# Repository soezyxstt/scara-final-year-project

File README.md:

# 2-DOF SCARA Robot | Final Year Project

Embedded control and web software for a planar 2-DOF SCARA robot used as an educational control-system demonstrator.

The repository includes ESP32 firmware, a browser HMI, shared telemetry definitions, experiment tools, documentation, and selected datasets.

## System

- Joint 1: DC motor with closed-loop control
- Joint 2: stepper motor
- Controller: ESP32 DevKit V1
- HMI: Next.js in the browser
- Communication: Web Serial at 921600 baud

The firmware implements PID control, a tracking differentiator, trapezoidal trajectories, and switchable inertia, Coriolis, and gravity compensation.

## Highlights

- Closed-loop embedded control
- Cartesian trajectory generation and inverse kinematics
- Shared telemetry contract between firmware and HMI
- Browser-based tuning, monitoring, and experiment analysis
- Reproducible experiment export pipeline

## Architecture

```text
SCARA hardware
      │
      ▼
    ESP32
  control + trajectory
      │
   Web Serial
      │
      ▼
 Browser HMI
 operation + telemetry + analysis
```

## Structure

```text
analysis/          experiment export tools
data/experiments/  selected datasets
firmware/          PlatformIO firmware
hmi/               Next.js HMI
shared/telemetry/  shared packet schema
docs/              technical documentation
```

## Run the HMI

```bash
npm install
npm run gen
npm run dev
```

Use Chrome or Edge for Web Serial.

## Firmware

```powershell
scara.bat compile
scara.bat upload
scara.bat all
```

## Experiments

| Experiment | Comparison |
|---|---|
| EXP-1 | tracking differentiator off vs on |
| EXP-2 | dynamic compensation off vs inertia on |
| EXP-3 | inertia only vs inertia + Coriolis |
| EXP-4 | gravity compensation off vs on |
| EXP-5 | trapezoidal profile off vs on |

Recreate selected exports with:

```powershell
python analysis/export_experiment_csv.py ..\results\tugasakhir.db
```

See `data/README.md` and `docs/` for technical details.

Never commit credentials, environment files, or raw application databases. Verify workspace limits and engage the emergency stop before working on the mechanism.

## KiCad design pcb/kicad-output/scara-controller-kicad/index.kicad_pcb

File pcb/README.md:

# SCARA Controller PCB (tscircuit)

ESP32 DevKitC "motherboard" that sockets an A4988 stepper driver carrier and
an LM2596 buck module (no-LED variant), regulates power, and breaks out the
potentiometer, quadrature-encoder, and off-board L298N control signals.

This board does **not** require you to solder the MCU or the driver chip by
hand — you buy the ESP32 DevKitC, the A4988 carrier, and the LM2596 module
separately, and they plug into headers/sockets on this PCB (same idea as a
RAMPS/CNC-shield board).

**Pin assignments match `firmware/include/config.h` 1:1.** The Joint 1 DC
motor is driven by an **off-board L298N H-bridge** — this PCB does not carry
the H-bridge itself, it breaks out 12V/5V/GND plus the three control signals
(IN3=IO16, IN4=IO17, EN=IO18) to the `J_DC` header. A new 4-pin `J_ENC`
header adds a quadrature encoder (A=IO25, B=IO26) for closed-loop Joint 1
feedback.

**Grounding:** a solid bottom-layer copper pour tied to `net.GND` acts as the
ground plane; every GND pad ties to it. Rails are named nets (`V12`, `V5`,
`V3V3`, `GND`) so the schematic renders clean power/ground flags.

> **On bottom-layer "slots":** the bottom layer looks busy, but most of those
> traces are the **GND membership tree** — they carry `net.GND` and merge into
> the pour (same net), so they do **not** cut the plane. The only true plane
> slots are a handful of non-GND escapes routed on the bottom to clear the dense
> through-hole pad fields (notably `STEP` and the `5V` dip). They are deliberate
> and load-bearing (moving them to the top layer would re-introduce pad-field
> DRC violations), and at this board's signal speeds (`STEP`/PWM ≤ tens of kHz)
> the return-path impact of these short slots is negligible. `DIR` and `V12`
> were routed along the board margin **outside** the pour boundary, so they
> don't slot it at all.

## What's been verified

This design has been built and checked with tscircuit's own DRC/connectivity
checker (`@tscircuit/core`) — **0 errors**: no shorts, no missing nets, no
pad-clearance violations, no footprint overlaps. What has **not** been
verified: exact manufacturable footprints for the ESP32 DevKitC header pitch
and the A4988 socket pitch — those use best-known nominal dimensions, but you
should confirm them against your actual boards before ordering copper (see
"Before you fab" below).

## Setup (on your own machine — this needs internet access)

```bash
# 1. Install bun (tscircuit's CLI requires it)
curl -fsSL https://bun.sh/install | bash

# 2. Install dependencies
cd .temp
bun install --ignore-scripts   # --ignore-scripts works around a sharp/Windows install crash

# 3. Live preview (schematic + PCB + 3D, hot reload like Next.js)
npx tscircuit dev
# open http://localhost:3020
```

## Files

- `index.tsx` — the board. Default export, this is what `tsci dev` renders.
- `validate.tsx` — headless DRC/connectivity check script. Run with
  `bun run validate.tsx`.
- `package.json`, `tsconfig.json` — minimal config to run both of the above.

## Bill of materials (besides the PCB itself)

| Ref | Part | Notes |
|---|---|---|
| U1 | ESP32 DevKitC (38-pin) | Socketed via 2× 1×19, 2.54mm female headers, 25.4mm row spacing. Onboard USB-UART, 3.3V LDO, EN/BOOT buttons — none of that is duplicated on this PCB. |
| A4988 | A4988 stepper driver carrier (Pololu or clone) | Joint 2. Plugs into the A4988 socket. MS1/MS2/MS3 are tied to 3V3 on the board (fixed 1/16 step); EN tied to GND (always enabled); RESET+SLEEP tied together to 3V3. |
| U2 | LM2596 adjustable buck module — no-LED version | 12V→5V. Modeled on the real full-size "LM2596S ADJ" module (~43×21mm): IN+/IN- on the left edge, OUT+/OUT- on the right edge, current flows left-to-right. |
| PWR_IN | 3-pin terminal (stand-in for a 5.5×2.1mm female DC barrel jack) | 12V supply in. VCC (center pin), GND (sleeve), and the normally-closed switch/detect leg (tied to GND). |
| STEPPER | 4-pin terminal | Joint 2 stepper motor coils (1A/1B/2A/2B). |
| J_DC | 6-pin header | Off-board **L298N** breakout for the Joint 1 DC motor: V12, GND, IN3=IO16, IN4=IO17, ENA=IO18, V5. |
| POT1 | 3-pin header | Joint 1 (DC) position pot → IO39. Brush-EMI filtering is done off-board (external LPF); no on-board bypass cap on this revision. |
| POT2 | 3-pin header | Joint 2 (stepper) position pot → IO36. No on-board bypass cap on this revision. |
| ENC | 4-pin header | Joint 1 quadrature encoder: 3V3, GND, ENC_A=IO25, ENC_B=IO26. |
| J_EXP | 8-pos 3.5mm screw terminal | Spare-GPIO expansion for future sensors: 3V3, GND, IO21 (I2C SDA), IO22 (I2C SCL), IO19, IO23, IO5, IO4 (ADC2). All firmware-untouched. IO5 is boot-strapping (idles HIGH) — don't pull LOW at power-on. (IO27/IO34 were remapped here onto the ESP32 right column so expansion nets don't cross the DIP.) |

## ESP32 GPIO map (matches `firmware/include/config.h`)

| Signal | GPIO | Why |
|---|---|---|
| Stepper STEP | IO14 | A4988 step pulse (J2) |
| Stepper DIR | IO12 | A4988 direction (J2) |
| Stepper MS1/MS2/MS3 | tied to 3V3 | fixed 1/16 microstep — firmware never toggles them, so they are hardwired (frees IO33/32/35 and removes the IO35 input-only bug) |
| DC motor IN3 | IO16 | L298N direction A (J1, via J_DC) |
| DC motor IN4 | IO17 | L298N direction B (J1, via J_DC) |
| DC motor EN | IO18 | L298N PWM speed, LEDC (J1, via J_DC) |
| Joint 2 pot wiper | IO36 | ADC1_CH0 — readable while WiFi is on |
| Joint 1 pot wiper | IO39 | ADC1_CH3 — RC-filtered (brush EMI) |
| Encoder A | IO25 | Joint 1 quadrature encoder (new) |
| Encoder B | IO26 | Joint 1 quadrature encoder (new) |

Four rails exist on this board: `V12`, `V5`, `V3V3`, and `GND`. The DevKitC's
own onboard regulator produces 3.3V, which is pulled back out of its `3V3` pin
(the `V3V3` net) to power the A4988 logic (`VDD`), the hardwired MS pins, the
pots, and the encoder header. `GND` is a solid bottom-layer copper pour.

## What changed in the manufacturing revision

This revision realigns the board to the **actual firmware** (`config.h`),
which drives a Joint 1 DC motor and reads two pots — earlier drafts had the
pins and the DC-motor handling wrong.

- **Pins now match `config.h` 1:1**: STEP=IO14, DIR=IO12, J2 pot=IO36, J1
  pot=IO39, and DC-motor control IN3/IN4/EN=IO16/IO17/IO18. (Previous draft
  had STEP=IO25, pots on IO34/35, encoder on IO16/17 — none of which the
  firmware uses.)
- **DC motor restored as an off-board L298N**: added the `J_DC` 6-pin header
  (V12/GND/IN3/IN4/ENA/V5). The firmware actively PWMs an L298N for Joint 1,
  so the previous "this board does not drive a DC motor" stance was wrong.
  The H-bridge stays off-board; only power + the three control signals are
  broken out.
- **Encoder kept, moved off the conflict**: `ENC` (A/B) now uses IO25/IO26
  because IO16/IO17 are taken by the L298N. This adds the closed-loop Joint 1
  feedback the new board was built for.
- **Microstep pins hardwired**: MS1/MS2/MS3 tie to 3V3 on the PCB (fixed 1/16
  step). This frees IO33/IO32/IO35 and removes the latent bug where MS3 sat on
  input-only IO35 and could not be driven.
- **Ground plane**: added a solid bottom-layer `copperpour` on `net.GND` and
  replaced the fragile hand-routed star-ground chain with per-pad ties to the
  net. Rails are named nets so the schematic gets proper power/ground flags.
- **J1 analog filtering is off-board**: the main brush-EMI low-pass is handled
  by an off-board LPF, so neither an on-board series resistor nor a local bypass
  cap is fitted at IO39 — this avoids double-filtering and excess ADC source
  impedance. (Earlier drafts listed `C_POT1`/`C_POT2` bypass caps; they were
  never placed in the layout and have been dropped from the docs to match.)
- **Spacing & size**: the `PWR_IN` silkscreen no longer overhangs the board
  edge, and the LM2596↔ESP32 gap was opened up. The board is tightly packed
  at **96×66mm** — width is set by the 43mm LM2596 + ESP32 + right-edge
  terminals; the rest of the empty space was trimmed out.
- **Expansion terminal**: added `J_EXP`, an 8-position 3.5mm screw terminal
  breaking out spare GPIO (I2C + digital + an ADC1 analog-in) plus 3V3/GND for
  future sensors, with per-pin silkscreen labels.

## Before you fab (i.e. before you actually order copper)

1. **Swap in real footprints.** The DevKitC header pitch/spacing and the
   A4988 socket pitch were built from best-known nominal dimensions. Once
   you're in `tsci dev` with real internet, use the part-import dialog to
   confirm:
   - your specific ESP32 DevKitC variant's row spacing (commonly 25.4mm, but
     some narrower clones use ~22.86mm)
   - your A4988/Pololu module's exact pin spacing
   - a real female DC barrel jack footprint in place of the `PWR_IN`
     3-pin terminal placeholder
2. **Trace widths.** Per-trace width is set with the **`thickness`** prop on
   `<trace>` (the `pcbRouteWidth` prop is silently ignored by this autorouter —
   don't use it). The board `minTraceWidth` floor is **0.5mm**; power/coil nets
   are explicitly fatter: `V12` 0.8mm, stepper coils 0.8mm, `5V` 0.6mm, `V3V3`
   0.5mm. `GND`'s real return current rides the bottom pour.
3. **Pour review.** Review the GND pour stitching (the vias tying top traces to
   the bottom plane — the small dots you see in the layout view) before fab.
4. **Thermal reliefs (hand-soldering DFM).** tscircuit's `<copperpour>` ties
   through-hole GND pads to the bottom plane with a **solid** connection — it
   does **not** emit thermal-relief spokes (the prop set is `connectsTo` only;
   no thermal option exists). Almost every part here is a hand-soldered THT
   module, so a solid plane connection makes GND pins act as a heatsink and
   risks cold joints. Before fab, either (a) enable thermal reliefs on the GND
   plane in your CAM/Gerber tool (target: 0.254mm spoke width, 0.254mm air gap,
   0.508mm expansion), or (b) use a temperature-controlled iron with extra dwell
   on GND pins. This is a known tscircuit limitation, not a layout error.
5. **Firmware cleanup (optional).** Since MS1/2/3 are hardwired, you can drop
   the `MS1/MS2/MS3` defines and their `pinMode`/`digitalWrite` calls from the
   firmware — they now drive nothing. Harmless to leave, but tidier to remove.

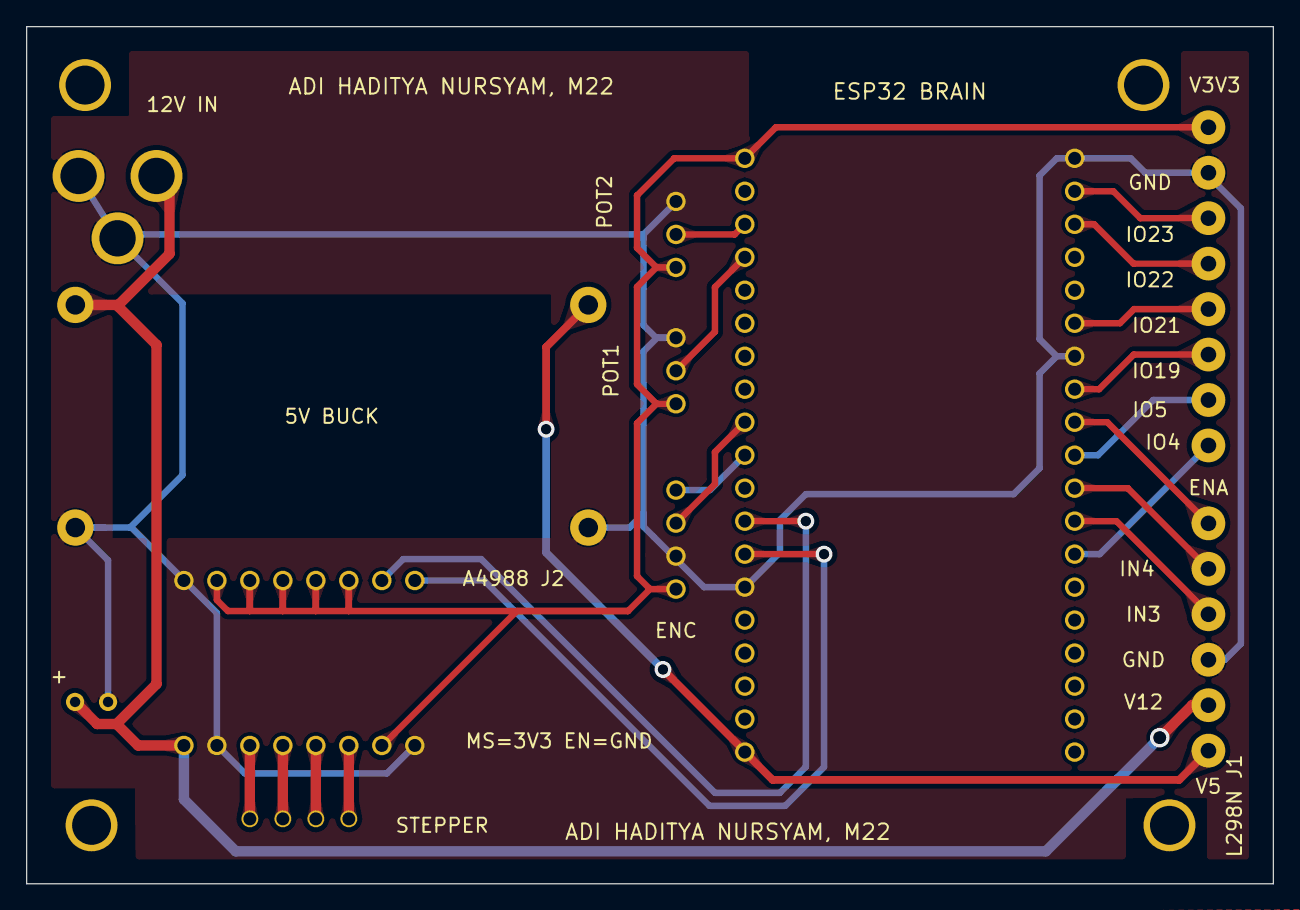
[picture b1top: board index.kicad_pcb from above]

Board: 2 copper layers, 96.0 x 66.0 mm, 11 parts (0 on the bottom side), 23 nets.

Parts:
A4988_SOCKET: A4988_SOCKET; connector
C_BULK: C_BULK; connector
ENC: ENC; connector
ESP32: ESP32; connector
J_DC: J_DC; connector
J_EXP: J_EXP; connector
LM2596: LM2596; connector
POT1: POT1; connector
POT2: POT2; connector
PWR_IN: PWR_IN; connector
STEPPER: STEPPER; connector

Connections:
.A4988_SOCKET > .1A to .STEPPER > .1A: A4988_SOCKET.12, STEPPER.2
.A4988_SOCKET > .1B to .STEPPER > .1B: A4988_SOCKET.11, STEPPER.1
.A4988_SOCKET > .2A to .STEPPER > .2A: A4988_SOCKET.13, STEPPER.3
.A4988_SOCKET > .2B to .STEPPER > .2B: A4988_SOCKET.14, STEPPER.4
.ESP32 > .IO12 to .A4988_SOCKET > .DIR: A4988_SOCKET.8, ESP32.13
.ESP32 > .IO14 to .A4988_SOCKET > .STEP: A4988_SOCKET.7, ESP32.12
.ESP32 > .IO16 to .J_DC > .IN3: ESP32.31, J_DC.3
.ESP32 > .IO17 to .J_DC > .IN4: ESP32.30, J_DC.2
.ESP32 > .IO18 to .J_DC > .ENA: ESP32.28, J_DC.1
.ESP32 > .IO19 to .J_EXP > .IO19: ESP32.27, J_EXP.6
.ESP32 > .IO21 to .J_EXP > .IO21: ESP32.25, J_EXP.5
.ESP32 > .IO22 to .J_EXP > .IO22: ESP32.22, J_EXP.4
.ESP32 > .IO23 to .J_EXP > .IO23: ESP32.21, J_EXP.3
.ESP32 > .IO25 to .ENC > .ENC_A: ENC.3, ESP32.9
.ESP32 > .IO26 to .ENC > .ENC_B: ENC.4, ESP32.10
.J_EXP > .IO4 to .ESP32 > .IO4: ESP32.32, J_EXP.8
.J_EXP > .IO5 to .ESP32 > .IO5: ESP32.29, J_EXP.7
.POT1 > .WIPER to .ESP32 > .IO39: ESP32.4, POT1.2
.POT2 > .WIPER to .ESP32 > .IO36: ESP32.3, POT2.2
GND: A4988_SOCKET.1, A4988_SOCKET.10, A4988_SOCKET.16, C_BULK.2, ENC.2, ESP32.14, ESP32.20, ESP32.26, J_DC.4, J_EXP.2, LM2596.2, LM2596.4, POT1.3, POT2.3, PWR_IN.1, PWR_IN.3
V3V3: A4988_SOCKET.2, A4988_SOCKET.3, A4988_SOCKET.4, A4988_SOCKET.5, A4988_SOCKET.6, A4988_SOCKET.15, ENC.1, ESP32.1, J_EXP.1, POT1.1, POT2.1
V5: ESP32.19, J_DC.6, LM2596.3
V12: A4988_SOCKET.9, C_BULK.1, J_DC.5, LM2596.1, PWR_IN.2

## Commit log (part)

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2026-06-05 change res to 10 bit and freq to 2k
2026-06-05 add dynamic pwm deadband and CTE chart
2026-06-05 add turborepo root
2026-06-05 add tailwindcss specific libs and rm redundant lock
2026-06-05 fix turborepo bugs
2026-06-05 fix ui bugs
2026-06-08 optimalize hmi
2026-06-08 add integrated file
2026-06-10 fix(hmi): resolve database constraint errors on save, implement expandable charts, and add dashboard xy workspace trace
2026-06-11 fix(hmi): improve color palette, adjust chart component colors, optimize chart performance, and resolve edge middleware build warning
2026-06-11 feat: implement SCARA AI Copilot, guided tutorial, soft dark theme, and fix prompt units
2026-06-11 style: simplify AI Copilot layout and remove double-scroll containers
2026-06-11 feat: add dynamic deadband and physical controller constraints to copilot prompt
2026-06-12 style: make top copilot bar sticky and integrate regenerate button
2026-06-12 feat(hmi): translate Indonesian UI elements to English and update command palette with vibrant icons
2026-06-12 Fix rest analysis tab and align J1 Controller Chart PWM simulation logic
2026-06-12 feat(trajectory): implement path splitting for inner workspace radius and update radius to 70.7mm
2026-06-12 feat: update workspace limits to 70.7 - 170 mm and -30 to 210 degrees sector
2026-06-14 fix xy trace flush timing and lower frac tresh at hold mode
2026-06-19 feat: add PCB viewer page, improve HMI analysis tabs, and update firmware
    - Add PCB interactive viewer page with schematic/assembly views
    - Enhance zn-analysis tab with view mode select and rest analysis
    - Update readme tab, capture menu, command palette, and chart panel
    - Add PCB context panel and tutorial updates
    - Fix implicit any types in build
    - Update firmware config, serial protocol, and control logic
2026-06-19 fix(pcb): constrain copper pour with boundary polygon and keepout zones
2026-06-19 refactor(pcb): replace LM2596 keepout with asymmetric copper pour boundary
2026-06-19 fix(pcb): widen high-current traces per IPC-2152 (12V 1.5mm, stepper coils 1.0mm)
2026-06-19 pcb: resolve mechanical overlaps, coaxial alignment, and trace clearances
2026-06-20 wider gaps between traces
2026-06-20 refactor(pcb): improve trace routing, add constants, and fix component positions
    - Extract PCB dimensions into constants.ts
    - Reduce plated hole outer diameter to 1.3mm
    - Add silkscreen outlines for JST, ESP32, A4988 bodies
    - Route V12, V5, STEP, DIR manually to avoid DRC violations
    - Replace GND traces with full bottom copper pour
    - Remap expansion pins IO27/IO34 to IO5/IO4 (keep nets on right column)
2026-06-24 add pcb
2026-06-24 fix11
